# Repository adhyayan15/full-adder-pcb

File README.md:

# Full Adder PCB

A 1-bit full-adder schematic and routed PCB I designed in KiCad during a PCB-design workshop. The design uses discrete 74LS-series logic ICs, switch inputs, and two LED outputs to explore binary addition in hardware.

**Status:** Schematic, PCB layout, and manufacturing exports are included. The image above is a KiCad render, not a photograph of an assembled board. Physical fabrication and testing are not documented in this repository; exported Gerbers do not by themselves establish manufacturing readiness.

## How a full adder works

A full adder adds three one-bit inputs: A, B, and carry-in (Cin). It produces a sum bit and carry-out (Cout).

- Sum = A XOR B XOR Cin
- Cout = (A AND B) OR (Cin AND (A XOR B))

| A | B | Cin | Sum | Cout |
|---|---|-----|-----|------|
| 0 | 0 | 0 | 0 | 0 |
| 0 | 0 | 1 | 1 | 0 |
| 0 | 1 | 0 | 1 | 0 |
| 0 | 1 | 1 | 0 | 1 |
| 1 | 0 | 0 | 1 | 0 |
| 1 | 0 | 1 | 0 | 1 |
| 1 | 1 | 0 | 0 | 1 |
| 1 | 1 | 1 | 1 | 1 |

This is the expected logic behavior, not a record of measured hardware results.

## Design files

| Folder | Contents |
|---|---|
| [hardware](hardware/) | Editable KiCad project, schematic, and routed PCB |
| [docs](docs/) | Schematic PDF exports and 3D board preview |
| [manufacturing](manufacturing/) | Front/back copper, solder mask, silkscreen, board outline, plated/non-plated drill files, and Gerber job file |

Open [the schematic PDF](docs/schematic.pdf) for a quick look without KiCad. A second supplied schematic export is preserved as `schematic-alternate-export.pdf`.

## Components in the schematic

| Reference | Component | Quantity |
|---|---|---:|
| U1 | 74LS86 XOR logic IC | 1 |
| U2 | 74LS08 AND logic IC | 1 |
| U3 | 74LS32 OR logic IC | 1 |
| SW1 | 8-position DIP switch | 1 |
| R1–R3 | 10 kΩ resistors | 3 |
| R4–R5 | 330 Ω resistors | 2 |
| D1–D2 | LEDs | 2 |

The schematic uses +5 V and GND power nets. The supplied Gerber job describes a two-layer, 1.6 mm board with an approximately 85.05 × 38.05 mm outline. These are exported design settings, not measured board dimensions.

## Open and inspect

1. Download or clone this repository.
2. Open `hardware/Full_Adder_PCB.kicad_pro` in KiCad. The supplied exports identify KiCad 10.0.6.
3. Use Schematic Editor to inspect the logic and PCB Editor to inspect placement and routing.
4. Open the Gerbers and drill files together in Gerber Viewer to inspect the exported layers.

Before ordering a board, run ERC and DRC, review any unconnected nets, and confirm power connections, IC supply decoupling, unused gate inputs, switch input levels, and LED drive against the component datasheets. No passing ERC/DRC report is included here.

### Interpreting the manufacturing exports

The [Gerber job file](manufacturing/Full_Adder_PCB-job.gbrjob) lists seven `.gbr` layer files under `FilesAttributes`; it does not list the two drill files. Include the drill files separately when reviewing the exported package:

- [Full_Adder_PCB-PTH.drl](manufacturing/Full_Adder_PCB-PTH.drl) contains the plated through-hole coordinates, with 0.800 mm and 0.900 mm drill tools declared in metric units.
- [Full_Adder_PCB-NPTH.drl](manufacturing/Full_Adder_PCB-NPTH.drl) is a non-plated drill export containing headers and an end marker but no drill tools or hole coordinates. Its presence does not indicate that mounting holes have been designed.

After a PCB edit, regenerate the Gerbers, job file, and drill outputs together, then inspect that exact set against the updated board. The checked-in exports are snapshots and do not update when the editable KiCad files change.

## Repository housekeeping

The source files and manufacturing exports retain the original design contents. Upload-added filename suffixes were removed so the KiCad project files share a base name and the Gerber job references resolve correctly. Temporary KiCad lock files and machine-local `.kicad_prl` settings are excluded.

Designed by **Adhyayan Tiwari**.

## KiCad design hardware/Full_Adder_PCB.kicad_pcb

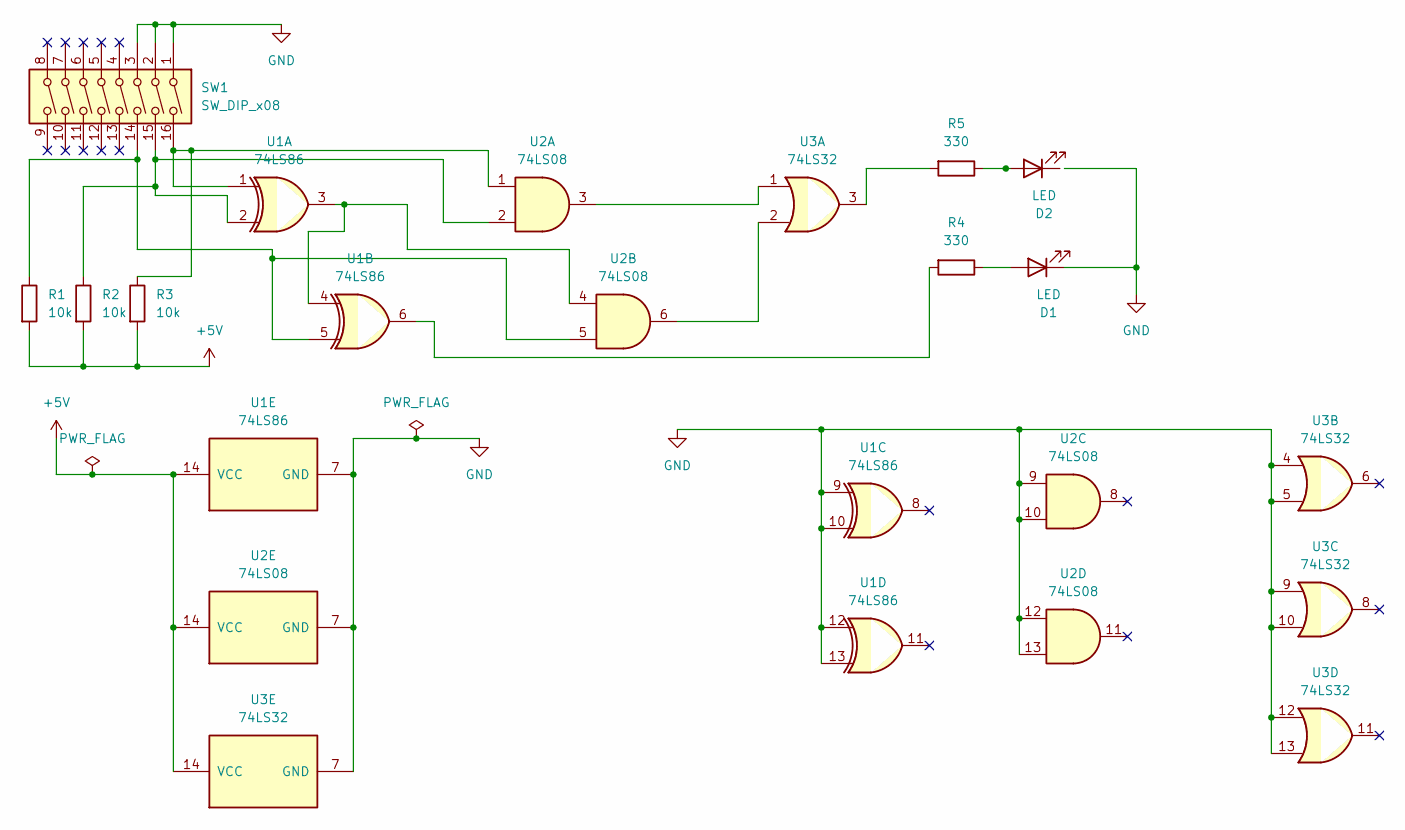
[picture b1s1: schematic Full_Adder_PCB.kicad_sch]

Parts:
D1, D2: LED; LED_D3.0mm
R1, R2, R3: 10k; R_Axial_DIN0207_L6.3mm_D2.5mm_P7.62mm_Horizontal
R4, R5: 330; R_Axial_DIN0207_L6.3mm_D2.5mm_P7.62mm_Horizontal
SW1: SW_DIP_x08; SW_DIP_SPSTx08_Slide_9.78x22.5mm_W7.62mm_P2.54mm
U1: 74LS86; DIP-14_W7.62mm
U2: 74LS08; DIP-14_W7.62mm
U3: 74LS32; DIP-14_W7.62mm

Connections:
+5V: R1.2, R2.2, R3.2, U1.14 (VCC), U2.14 (VCC), U3.14 (VCC)
GND: D1.1 (K), SW1.1, SW1.2, SW1.3, U1.7 (GND), U1.9, U1.10, U1.12, U1.13, U2.7 (GND), U2.9, U2.10, U2.12, U2.13, U3.4, U3.5, U3.7 (GND), U3.9, U3.10, U3.12, U3.13
unnamed: D1.2 (A), R4.1
unnamed: D2.2 (A_2), R5.1
unnamed: R1.1, SW1.14, U1.5, U2.5
unnamed: R2.1, SW1.15, U1.2, U2.2
unnamed: R3.1, SW1.16, U1.1, U2.1
unnamed: R4.2, U1.6
unnamed: R5.2, U3.3
unnamed: U1.3, U1.4, U2.4
unnamed: U2.3, U3.1
unnamed: U2.6, U3.2

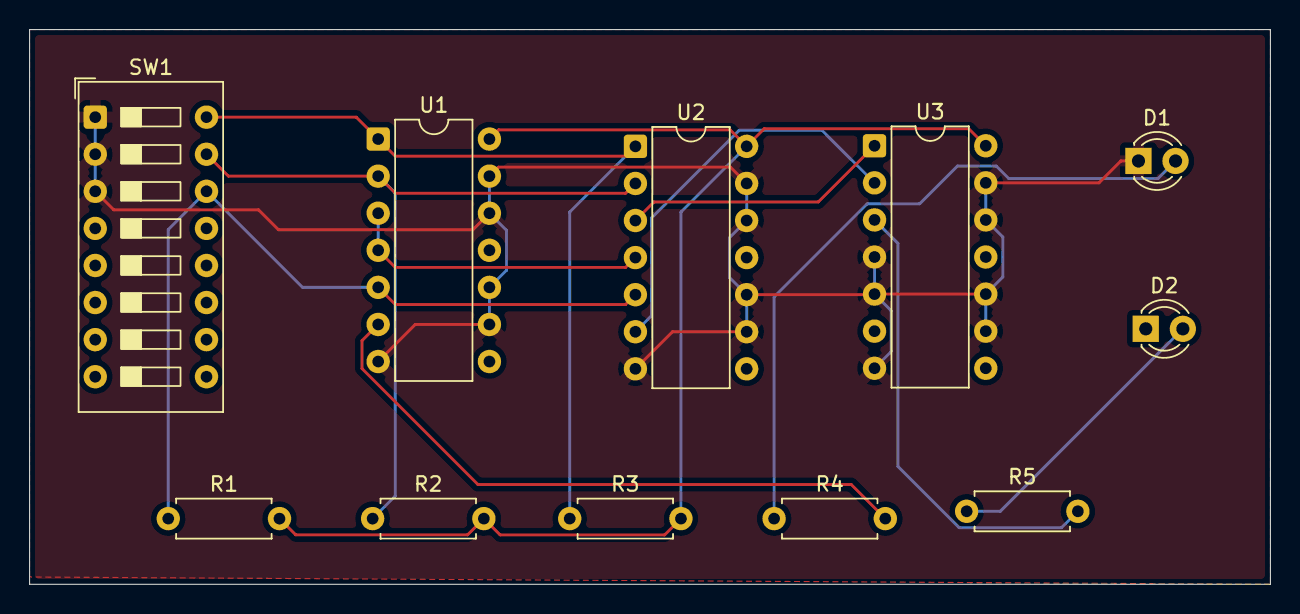
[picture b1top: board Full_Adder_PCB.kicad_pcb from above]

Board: 2 copper layers, 85.0 x 38.0 mm, 11 parts (0 on the bottom side), 12 nets.
